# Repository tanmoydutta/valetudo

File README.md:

# Valetudo, a BLE enabled ePaper fridge magnet module
It is a Module to show information on a 1.54" 200 x 200 pixel Black and White ePaper display. Together with a suitable 3D printed housing it can be used as a fridge magnet to display useful information. 

Below is the built module running a test sketch -

This is an OSHWA certified hardware - 
<p align="center">
  
</p>

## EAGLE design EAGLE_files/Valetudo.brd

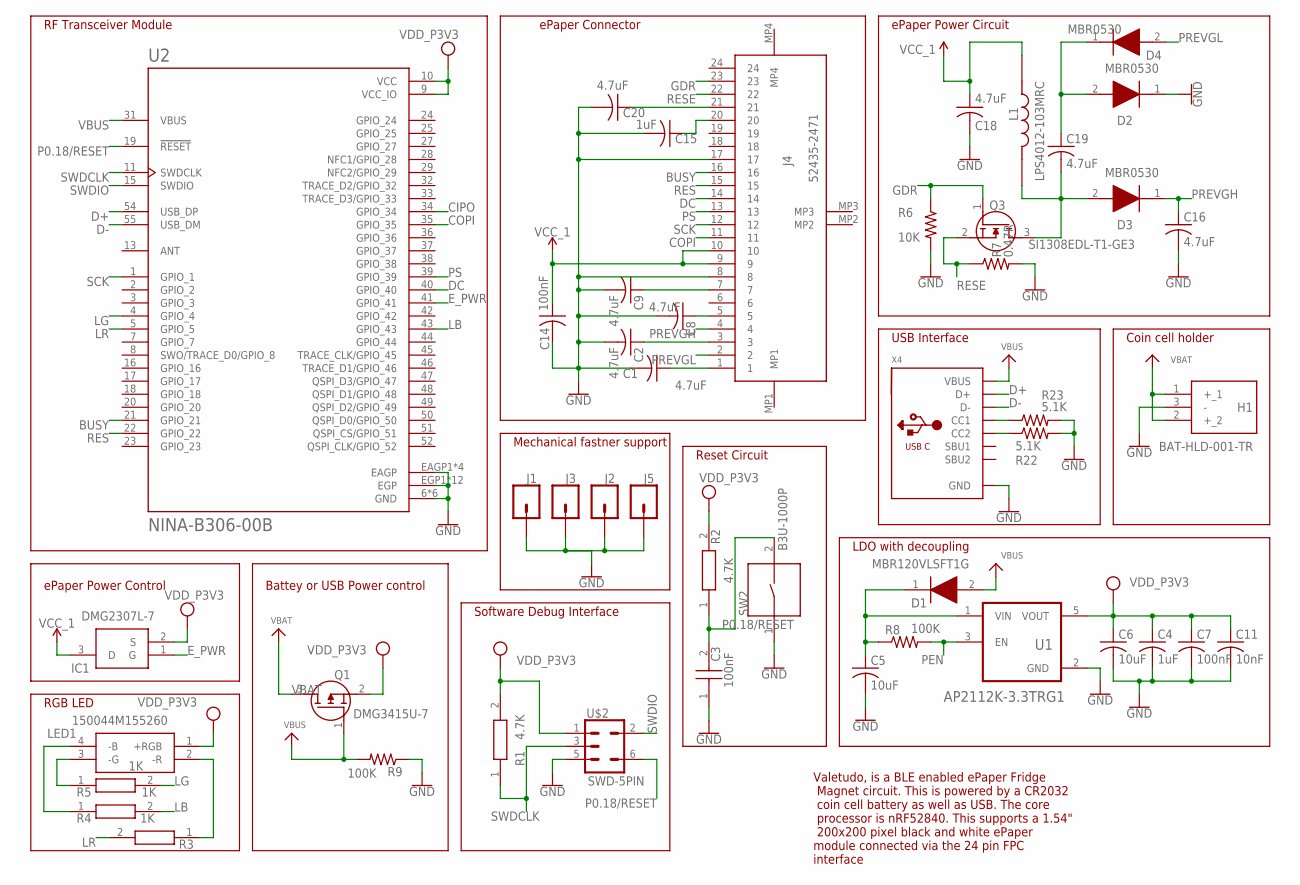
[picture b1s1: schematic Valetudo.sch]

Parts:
C1, C2, C8, C9, C16, C18, C19, C20: 4.7uF; C0402
C3: 100nF; CAPC1005X55N
C4, C15: 1uF; C0402
C5, C6: 10uF; C0402
C7, C14: 100nF; C0402
C11: 10nF; C0402
D1: MBR120VLSFT1G; SODFL3616X98N
D2, D3, D4: MBR0530; SOD3716X135N
H1: BAT-HLD-001-TR; BATHLD001TR
IC1: DMG2307L-7; SOT96P240X110-3N
J1, J2, J3, J5: CONN_01PTH_2MM; 1X01_2MM
J4: 52435-2471; 524352471
L1: LPS4012-103MRC; IND_LPS4012-103MRC
LED1: 150044M155260
Q1: DMG3415U-7; SOT96P240X100-3N
Q3: SI1308EDL-T1-GE3; SOT65P210X110-3N
R1, R2: 4.7K; RESC1005X40N
R3, R4, R5: 1K; RESC1005X40N
R6: 10K; R0402
R7: 0.47R; R0402
R8, R9: 100K; R0402
R22, R23: 5.1K; R0402
SW2: B3U-1000P; SW_B3U-1000P
U1: AP2112K-3.3TRG1; SOT95P285X140-5N
U2: NINA-B306-00B; XCVR_NINA-B306-00B
U$2: SWD-5PIN; PAD_05_03X2_TP_NO4
X4: MICROBUILDER_USB_C; MICROBUILDER_USB_C_CUSB31-CFM2AX-01-X

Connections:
BUSY: J4.16, U2.21 (GPIO_21)
CIPO: U2.34 (GPIO_34)
COPI: J4.11, U2.35 (GPIO_35)
D+: U2.54 (USB_DP), X4.A6 (D+), X4.B6 (D+)
D-: U2.55 (USB_DM), X4.A7 (D-), X4.B7 (D-)
DC: J4.14, U2.40 (GPIO_40)
E_PWR: IC1.1 (G), U2.41 (GPIO_41)
GDR: J4.23, Q3.1 (G), R6.1
GND: C1.2, C2.2, C3.1, C4.2, C5.2, C6.2, C7.2, C8.2, C9.2, C11.2, C14.2, C15.2, C16.2, C18.2, C20.2, D2.1 (K), H1.3 (-), J1.1, J2.1, J3.1, J4.8, J4.17, J5.1, R6.2, R7.2, R9.1, R22.2, R23.2, SW2.1, U1.2 (GND), U2.6 (GND), U2.12 (GND), U2.14 (GND), U2.26 (GND), U2.30 (GND), U2.53 (GND), U2.EAGP1 (EAGP), U2.EAGP2 (EAGP), U2.EAGP3 (EAGP), U2.EAGP4 (EAGP), U2.EGP1 (EGP), U2.EGP2 (EGP), U2.EGP3 (EGP), U2.EGP4 (EGP), U2.EGP5 (EGP), U2.EGP6 (EGP), U2.EGP7 (EGP), U2.EGP8 (EGP), U2.EGP9 (EGP), U2.EGP10 (EGP), U2.EGP11 (EGP), U2.EGP12 (EGP), U$2.5, X4.A1B12 (GND), X4.B1A12 (GND)
LB: R4.2, U2.43 (GPIO_43)
LG: R5.2, U2.4 (GPIO_4)
LR: R3.2, U2.5 (GPIO_5)
unnamed: LED1.4 (-B), R4.1
unnamed: LED1.3 (-G), R5.1
unnamed: LED1.2 (-R), R3.1
unnamed: C1.1, J4.1
unnamed: C19.1, D2.2 (A), D4.1 (K)
unnamed: R22.1, X4.B5 (CC2)
unnamed: C2.1, J4.3
unnamed: R23.1, X4.A5 (CC1)
unnamed: C5.1, D1.1 (K), R8.1, U1.1 (VIN)
unnamed: C19.2, D3.2 (A), L1.2, Q3.3 (D)
unnamed: C8.1, J4.5
unnamed: C9.1, J4.7
unnamed: C15.1, J4.20
unnamed: C20.1, J4.21
P0.18/RESET: C3.2, R2.1, SW2.2, U2.19 (!RESET), U$2.6
PEN: R8.2, U1.3 (EN)
PREVGH: C16.1, D3.1 (K), J4.4
PREVGL: D4.2 (A), J4.2
PS: J4.13, U2.39 (GPIO_39)
RES: J4.15, U2.22 (GPIO_22)
RESE: J4.22, Q3.2 (S), R7.1
SCK: J4.12, U2.1 (GPIO_1)
SWDCLK: R1.1, U2.11 (SWDCLK), U$2.3
SWDIO: U2.15 (SWDIO), U$2.2
VBAT: H1.1 (+_1), H1.2 (+_2), Q1.3 (D)
VBUS: D1.2 (A), Q1.1 (G), R9.2, U2.31 (VBUS), X4.A4B9 (VBUS), X4.B4A9 (VBUS)
VCC: C4.1, C6.1, C7.1, C11.1, IC1.2 (S), LED1.1 (+RGB), Q1.2 (S), R1.2, R2.2, U1.5 (VOUT), U2.9 (VCC_IO), U2.10 (VCC), U$2.1
VCC_1: C14.1, C18.1, IC1.3 (D), J4.9, J4.10, L1.1

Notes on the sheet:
Battey or USB Power control
RF Transceiver Module
LDO with decoupling
Reset Circuit
USB Interface
Software Debug Interface
Valetudo, is a BLE enabled ePaper Fridge Magnet circuit. This is powered by a CR2032 coin cell battery as well as USB. The core processor is nRF52840. This supports a 1.54" 200x200 pixel black and white ePaper module connected via the 24 pin FPC interface
RGB LED
ePaper Power Circuit
Mechanical fastner support
ePaper Connector
Coin cell holder
ePaper Power Control

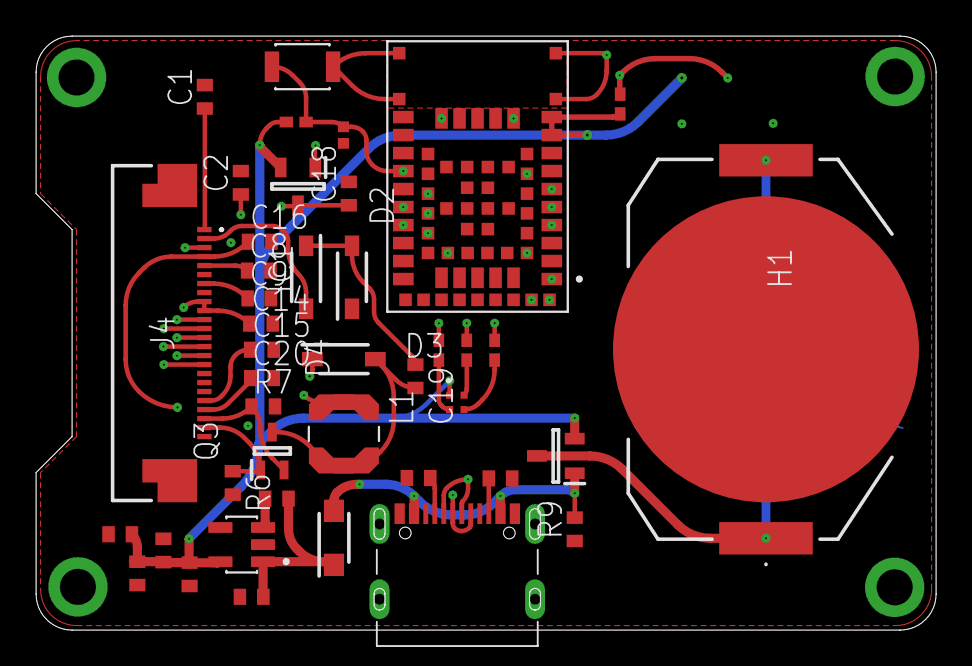
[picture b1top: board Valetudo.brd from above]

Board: 6 copper layers, 50.0 x 33.0 mm, 47 parts (1 on the bottom side), 39 nets.

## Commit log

2025-06-02 Adding new files
2025-06-02 Adding new files and some changes
2025-06-02 Update README.md
    First documentation with images and license.
2025-06-02 Update README.md
    Adjusted filename
2025-06-03 Adding Image
2025-06-04 3D files added
2025-06-05 OSGWA mark added
2025-06-19 Updates to board file
2025-06-23 Adding a sample sketch

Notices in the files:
parts and their libraries:
SparkFun-Connectors: Licensing: Creative Commons ShareAlike 4.0 International - https://creativecommons.org/licenses/by-sa/4.0
